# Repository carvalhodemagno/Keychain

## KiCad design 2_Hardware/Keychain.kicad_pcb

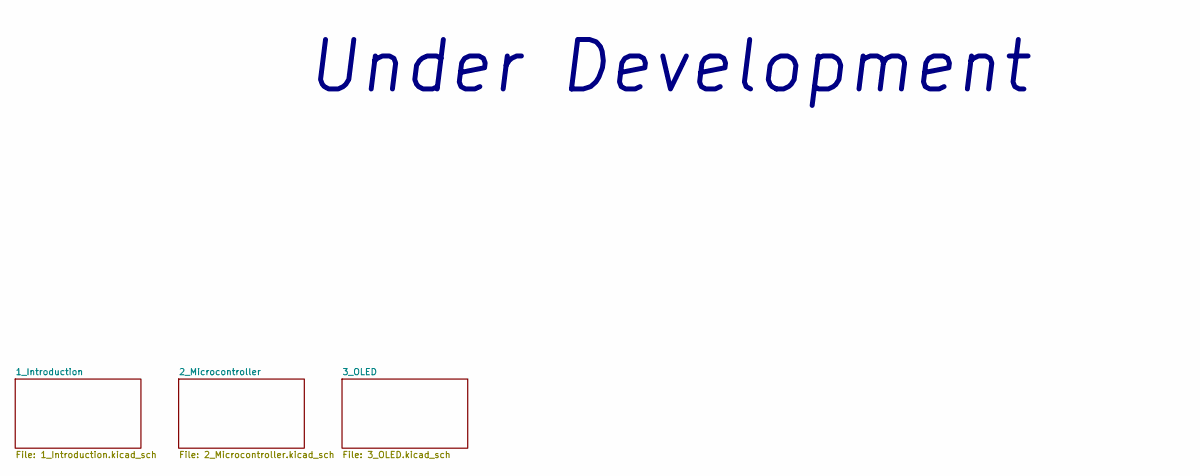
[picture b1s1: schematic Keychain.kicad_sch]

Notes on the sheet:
Under Development

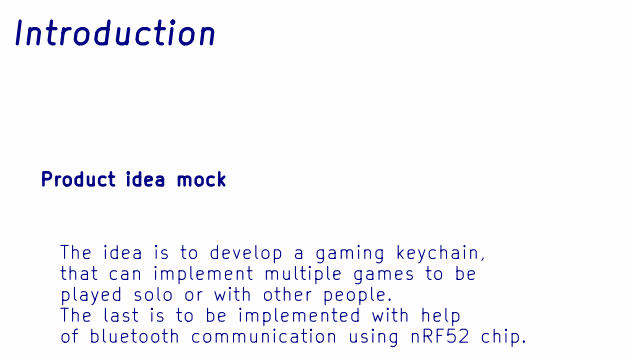
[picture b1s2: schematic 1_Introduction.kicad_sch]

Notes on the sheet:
Product idea mock
The idea is to develop a gaming keychain, that can implement multiple games to be played solo or with other people. The last is to be implemented with help of bluetooth communication using nRF52 chip.
Introduction

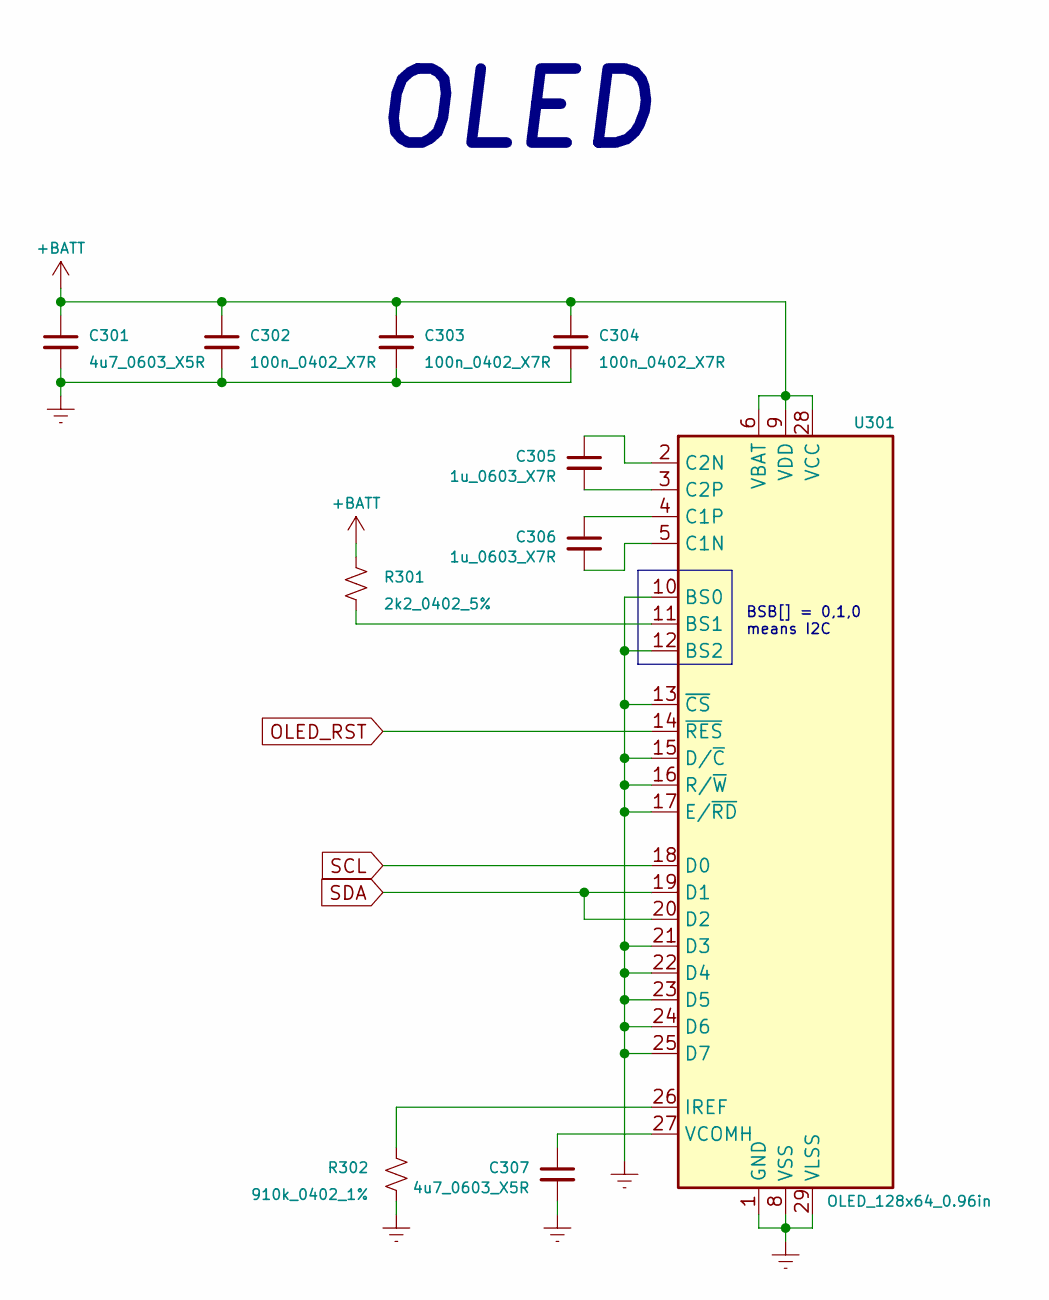
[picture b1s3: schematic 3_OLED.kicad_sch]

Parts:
C301, C307: 4u7_0603_X5R; C_0603_1608Metric
C302, C303, C304: 100n_0402_X7R; C_0402_1005Metric
C305, C306: 1u_0603_X7R; C_0603_1608Metric
R301: 2k2_0402_5%; R_0402_1005Metric
R302: 910k_0402_1%; R_0402_1005Metric
U301: OLED_128x64_0.96in; OLED

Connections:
+BATT: C301.1, C302.1, C303.1, C304.1, R301.1, U301.6 (VBAT), U301.9 (VDD), U301.28 (VCC); also elsewhere on the board
Earth: C301.2, C302.2, C303.2, C304.2, C307.2, R302.2, U301.1 (GND), U301.8 (VSS), U301.10 (BS0), U301.12 (BS2), U301.13 (~CS), U301.15 (D/~C), U301.16 (R/~W), U301.17 (E/~RD), U301.21 (D3), U301.22 (D4), U301.23 (D5), U301.24 (D6), U301.25 (D7), U301.29 (VLSS), U301.30 (GND); also elsewhere on the board
unnamed: C305.1, U301.2 (C2N)
unnamed: C305.2, U301.3 (C2P)
unnamed: C306.1, U301.4 (C1P)
unnamed: C306.2, U301.5 (C1N)
unnamed: C307.1, U301.27 (VCOMH)
unnamed: R301.2, U301.11 (BS1)
unnamed: R302.1, U301.26 (IREF)
OLED_RST: U301.14 (~RES); also elsewhere on the board
SCL: U301.18 (D0); also elsewhere on the board
SDA: U301.19 (D1), U301.20 (D2); also elsewhere on the board

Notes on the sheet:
BSB[] = 0,1,0 means I2C
OLED

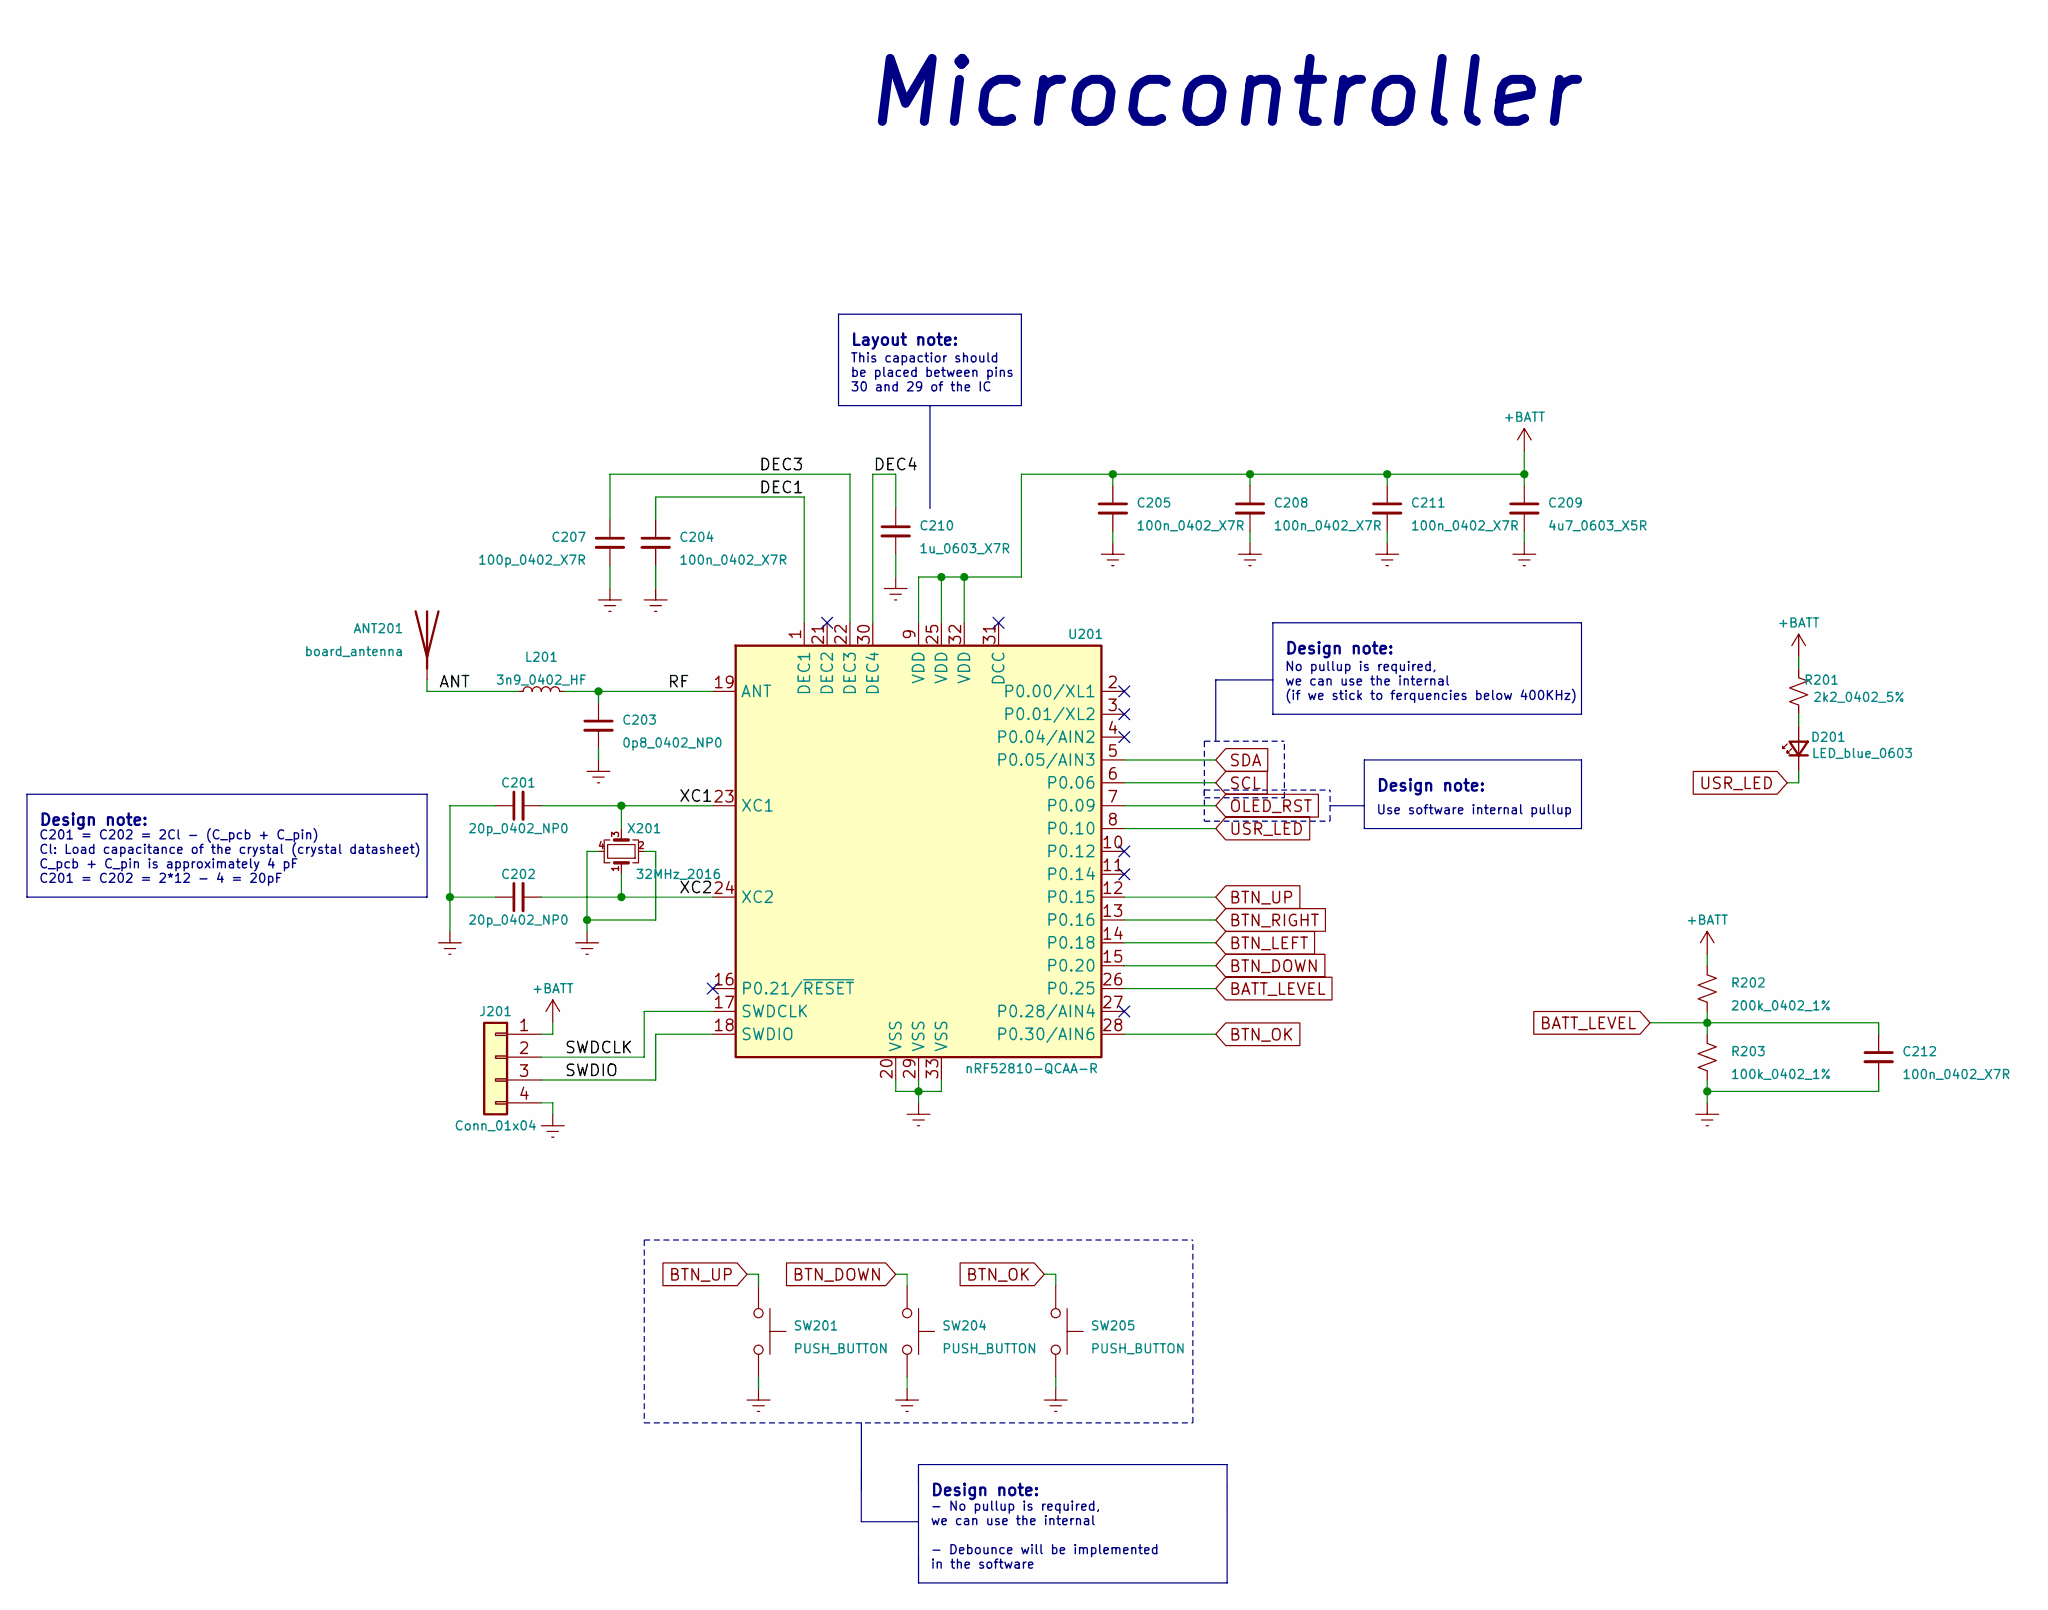
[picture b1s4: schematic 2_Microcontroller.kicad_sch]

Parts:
ANT201: board_antenna; nrf52_antenna
C201, C202: 20p_0402_NP0; C_0402_1005Metric
C203: 0p8_0402_NP0; C_0402_1005Metric
C204, C205, C208, C211, C212: 100n_0402_X7R; C_0402_1005Metric
C207: 100p_0402_X7R; C_0402_1005Metric
C209: 4u7_0603_X5R; C_0603_1608Metric
C210: 1u_0603_X7R; C_0603_1608Metric
D201: LED_blue_0603; LED_0603_1608Metric
J201: Conn_01x04; PinHeader_1x04_P2.54mm_Vertical
L201: 3n9_0402_HF; L_0402_1005Metric
R201: 2k2_0402_5%; R_0402_1005Metric
R202: 200k_0402_1%; R_0402_1005Metric
R203: 100k_0402_1%; R_0402_1005Metric
SW201, SW204, SW205: PUSH_BUTTON
U201: nRF52810-QCAA-R; QFN-32-1EP_5x5mm_P0.5mm_EP3.6x3.6mm
X201: 32MHz_2016; Crystal_SMD_2016-4Pin_2.0x1.6mm

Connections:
+BATT: C205.1, C208.1, C209.1, C211.1, J201.1, R201.1, R202.1, U201.9 (VDD), U201.25 (VDD), U201.32 (VDD); also elsewhere on the board
/2_Microcontroller/ANT: ANT201.1 (A), L201.1
/2_Microcontroller/DEC1: C204.1, U201.1 (DEC1)
/2_Microcontroller/DEC3: C207.1, U201.22 (DEC3)
/2_Microcontroller/DEC4: C210.1, U201.30 (DEC4)
/2_Microcontroller/RF: C203.1, L201.2, U201.19 (ANT)
/2_Microcontroller/SWDCLK: J201.2, U201.17 (SWDCLK)
/2_Microcontroller/SWDIO: J201.3, U201.18 (SWDIO)
/2_Microcontroller/XC1: C201.2, U201.23 (XC1), X201.3
/2_Microcontroller/XC2: C202.2, U201.24 (XC2), X201.1
BATT_LEVEL: C212.1, R202.2, R203.1, U201.26 (P0.25)
BTN_DOWN: SW204.1, U201.15 (P0.20)
BTN_LEFT: U201.14 (P0.18)
BTN_OK: SW205.1, U201.28 (P0.30/AIN6)
BTN_RIGHT: U201.13 (P0.16)
BTN_UP: SW201.1, U201.12 (P0.15)
Earth: C201.1, C202.1, C203.2, C204.2, C205.2, C207.2, C208.2, C209.2, C210.2, C211.2, C212.2, J201.4, R203.2, SW201.2, SW204.2, SW205.2, U201.20 (VSS), U201.29 (VSS), U201.33 (VSS), X201.2, X201.4; also elsewhere on the board
unnamed: D201.2 (A), R201.2
OLED_RST: U201.7 (P0.09); also elsewhere on the board
SCL: U201.6 (P0.06); also elsewhere on the board
SDA: U201.5 (P0.05/AIN3); also elsewhere on the board
USR_LED: D201.1 (K), U201.8 (P0.10)

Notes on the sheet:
Microcontroller
This capactior should be placed between pins 30 and 29 of the IC
- No pullup is required, we can use the internal - Debounce will be implemented in the software
C201 = C202 = 2Cl - (C_pcb + C_pin) Cl: Load capacitance of the crystal (crystal datasheet) C_pcb + C_pin is approximately 4 pF C201 = C202 = 2*12 - 4 = 20pF
Design note:
Layout note:
No pullup is required, we can use the internal (if we stick to ferquencies below 400KHz)
Use software internal pullup

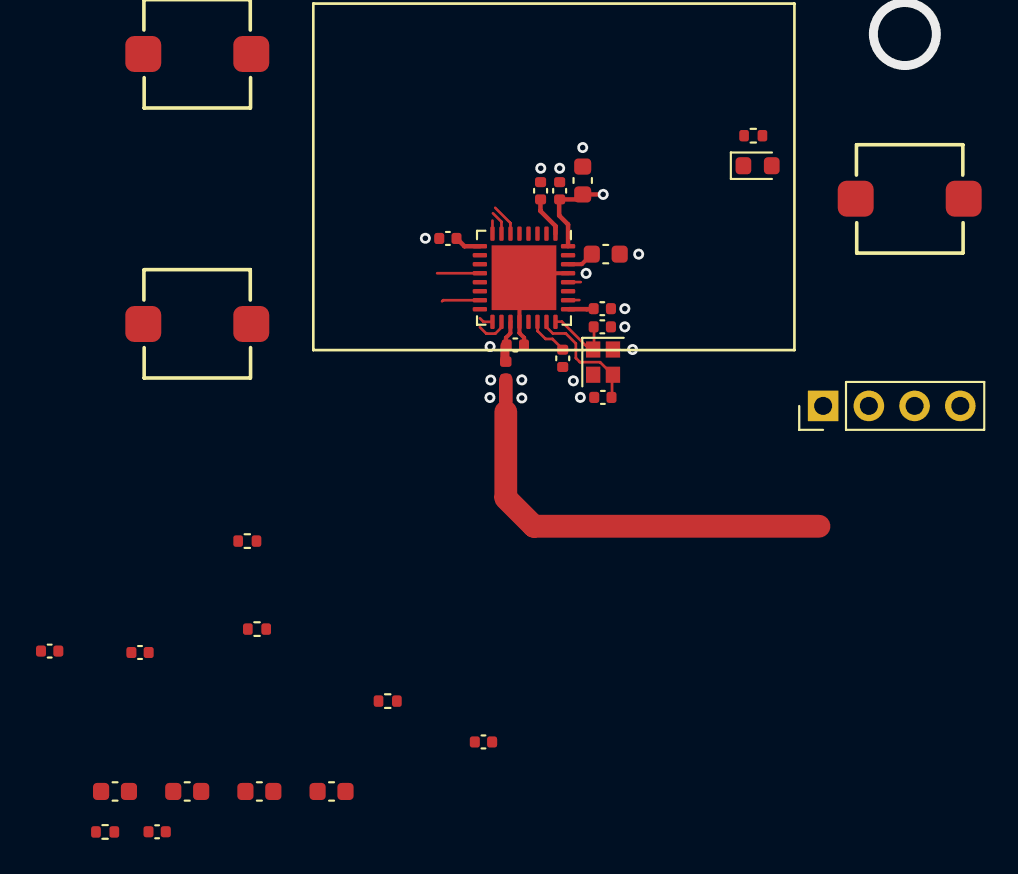
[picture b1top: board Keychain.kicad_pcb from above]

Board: 2 copper layers, 33 parts (1 on the bottom side), 27 nets.

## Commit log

2022-12-23 Adds the first version of the idea mockup
2023-01-07 adds firt draft of schematic files and start of pcb layout
